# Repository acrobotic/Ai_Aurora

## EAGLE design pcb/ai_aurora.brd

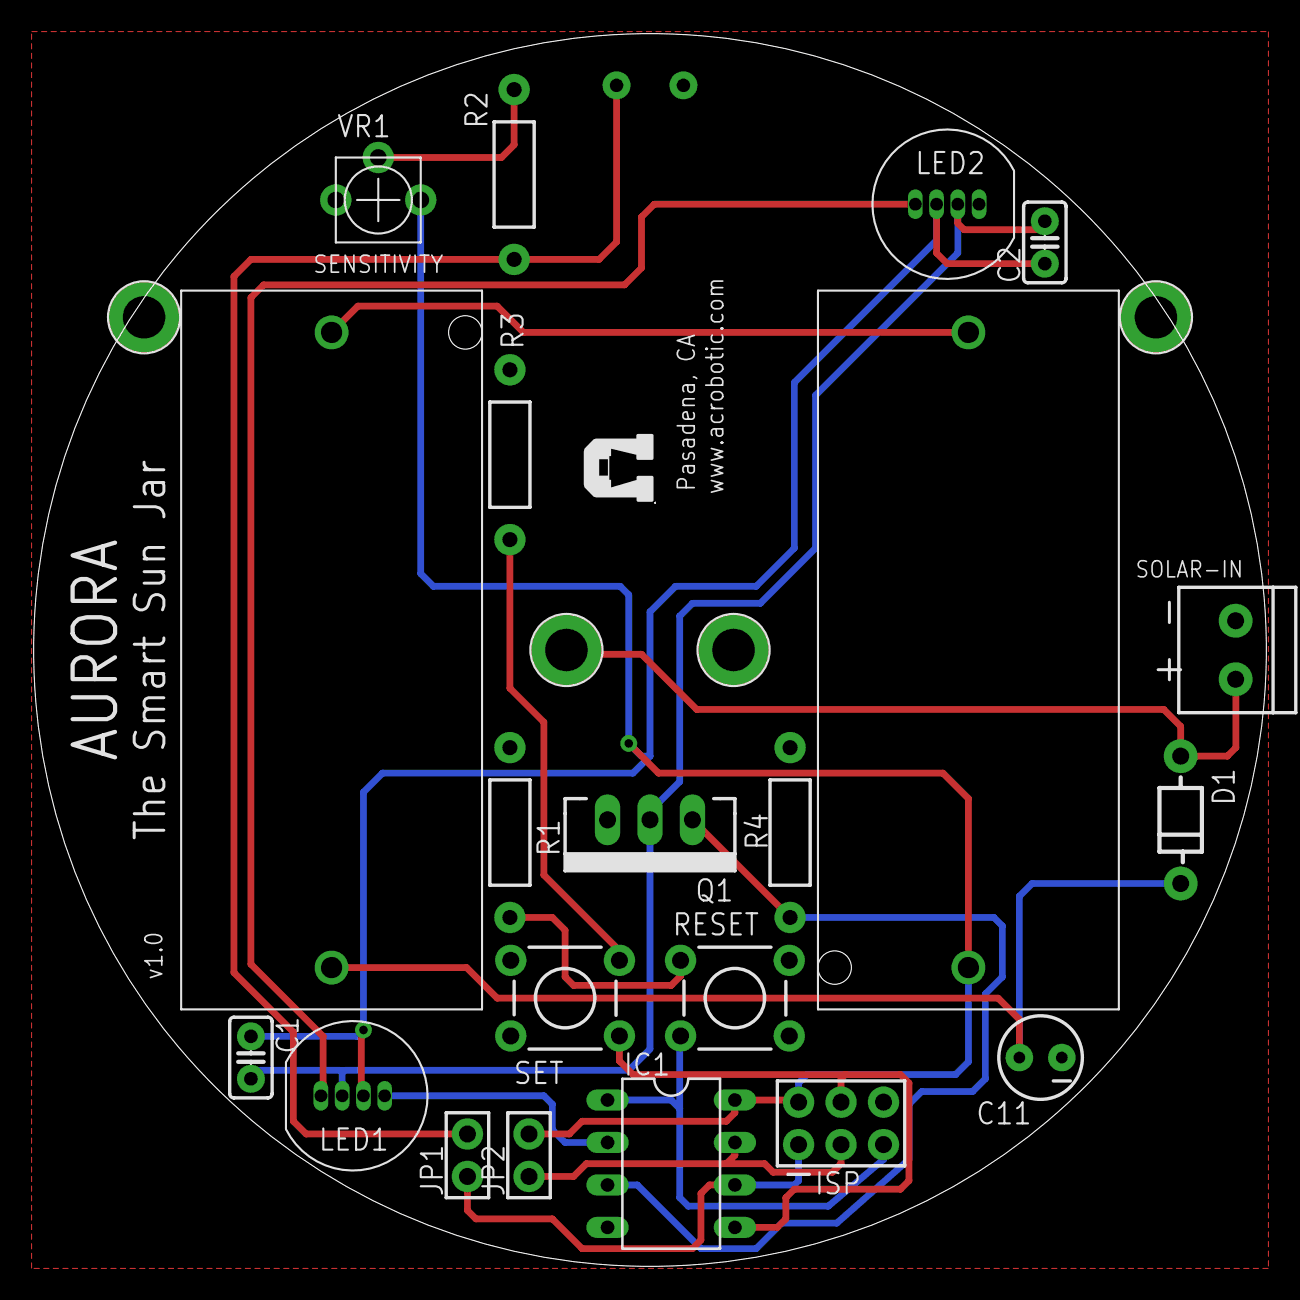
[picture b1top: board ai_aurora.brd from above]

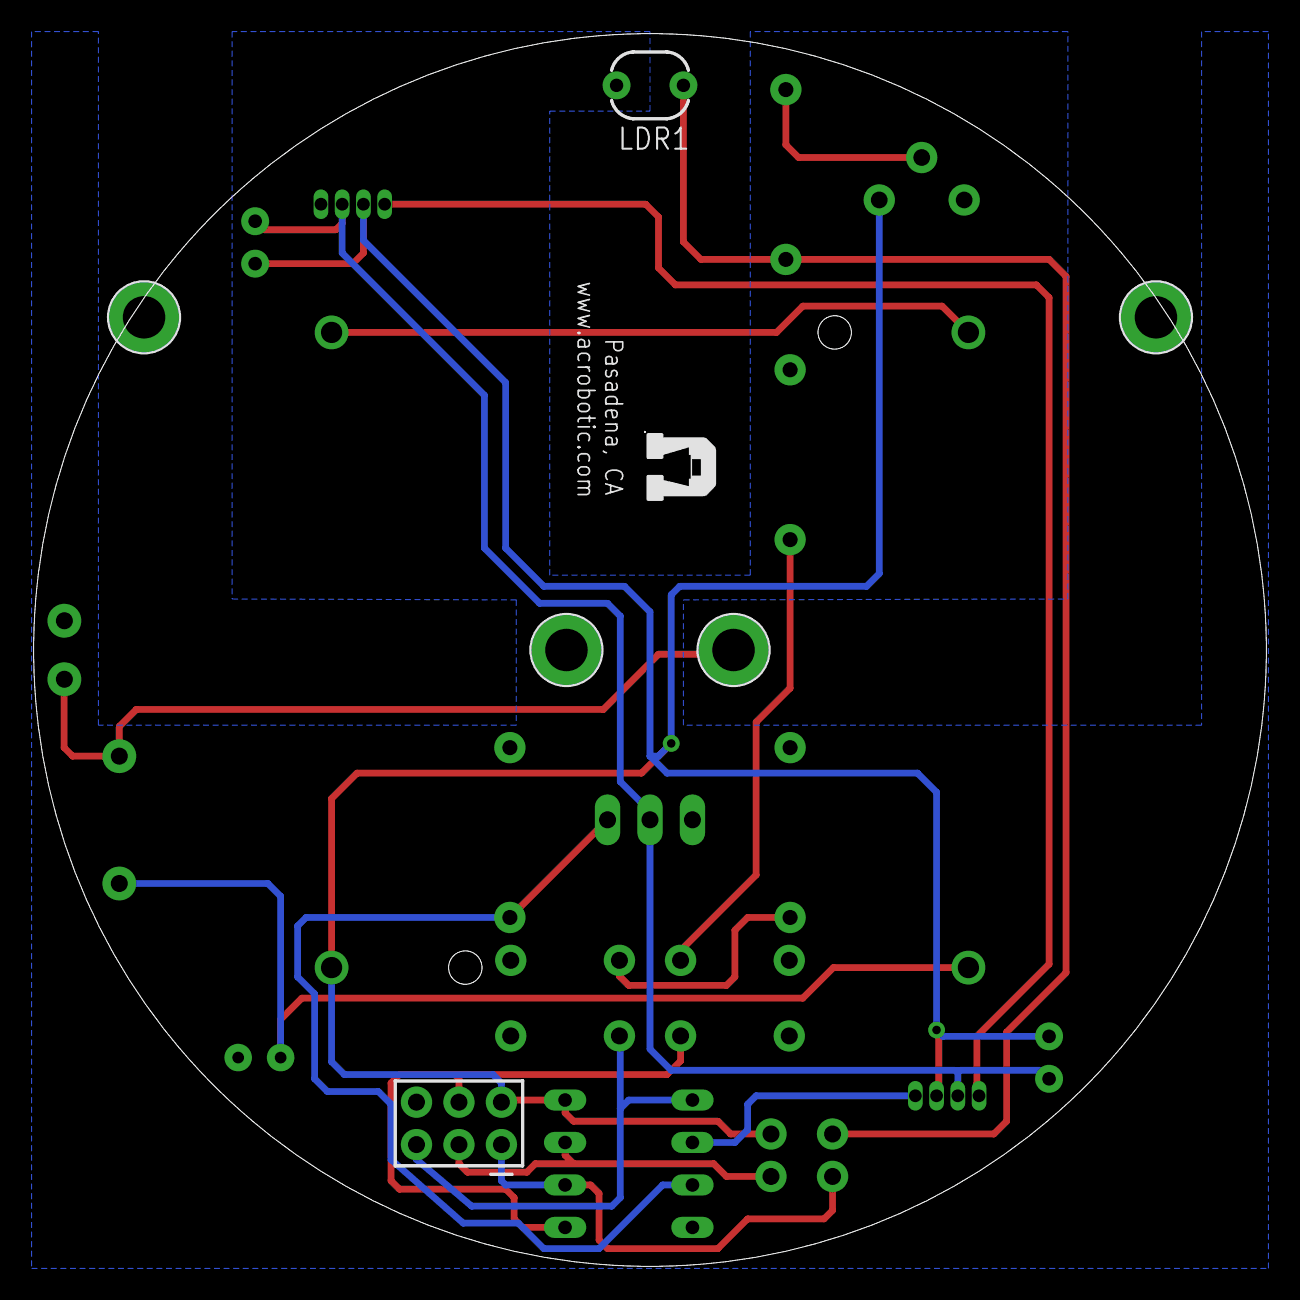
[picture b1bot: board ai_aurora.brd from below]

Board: 2 copper layers, 73.8 x 73.8 mm, 28 parts (2 on the bottom side), 17 nets.

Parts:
BAT1, BAT2: CR123A; BATTERY-CR123A
C1, C2: 0.1uF; CAP-025X050
C11: 4.7uF; CAP-POL-025X50
D1: TH-1N914
IC1: ATTINY85-DIP; DIL08
ISP: 2X03
JP1, JP2: 1X02-PJ; 1X02
LDR1: LDR-PTH; LDR
LED1, LED2: LED-PL9823-F8
M2, M3: 1X01-TERM-PANEL; 1X01-PANEL
PANEL+: 1X01-TERM-PANEL; 1X01-PANEL
PANEL-: 1X01-TERM-PANEL; 1X01-PANEL
Q1: FQP30N06L; TO-220
R1, R3: 10K; RES-AXIAL-0.4
R2, R4: 100K; RES-AXIAL-0.4
RESET: SW-SPSTTH06X06; SW-SPST-TH06X06
SET: SW-SPSTTH06X06; SW-SPST-TH06X06
SOLAR-IN: 1X02ST; 1X02-ST
U$4, U$5: AI-LOGOM; AI-LOGO-M
VR1: 1M; POT-05X05

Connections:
-: C1.2, C2.2, LED1.3, LED2.3, Q1.2
DI: IC1.2, LED1.1
GND: C11.C, IC1.4, ISP.6, LDR1.1, PANEL-.1, Q1.3, R1.P$1, R3.P$1, R4.P$1, SOLAR-IN.2
LED_EN: IC1.3, Q1.1, R4.P$2
MISO/LDR: IC1.6, ISP.1, JP1.1
MOSI/SET: IC1.5, ISP.4, SET.B@1
unnamed: BAT1.+, BAT2.-
unnamed: R1.P$2, RESET.B@1
unnamed: LED1.4, LED2.1
unnamed: R3.P$2, SET.A@1
unnamed: R2.P$2, VR1.2
unnamed: JP1.2, LDR1.2, R2.P$1
RST: IC1.1, ISP.5, RESET.A@1
SCK/BATT: IC1.7, ISP.3, JP2.1
VBAT: BAT2.+, C1.1, C2.1, IC1.8, ISP.2, JP2.2, LED1.2, LED2.2, VR1.3
VIN: BAT1.-, C11.A, D1.C
VPANEL: D1.A, PANEL+.1, SOLAR-IN.1

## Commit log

2014-10-26 schematic done
2014-10-27 some fitting issues remain
2014-11-04 updating
2014-11-04 improvements on the test firmware
2014-11-17 progress using ISR for pin change interrupt to switch on/off things
2014-11-24 updating firmware and pcb
2014-12-02 gerbers
2014-12-02 updated libraries
2014-12-02 minor update to schematic
